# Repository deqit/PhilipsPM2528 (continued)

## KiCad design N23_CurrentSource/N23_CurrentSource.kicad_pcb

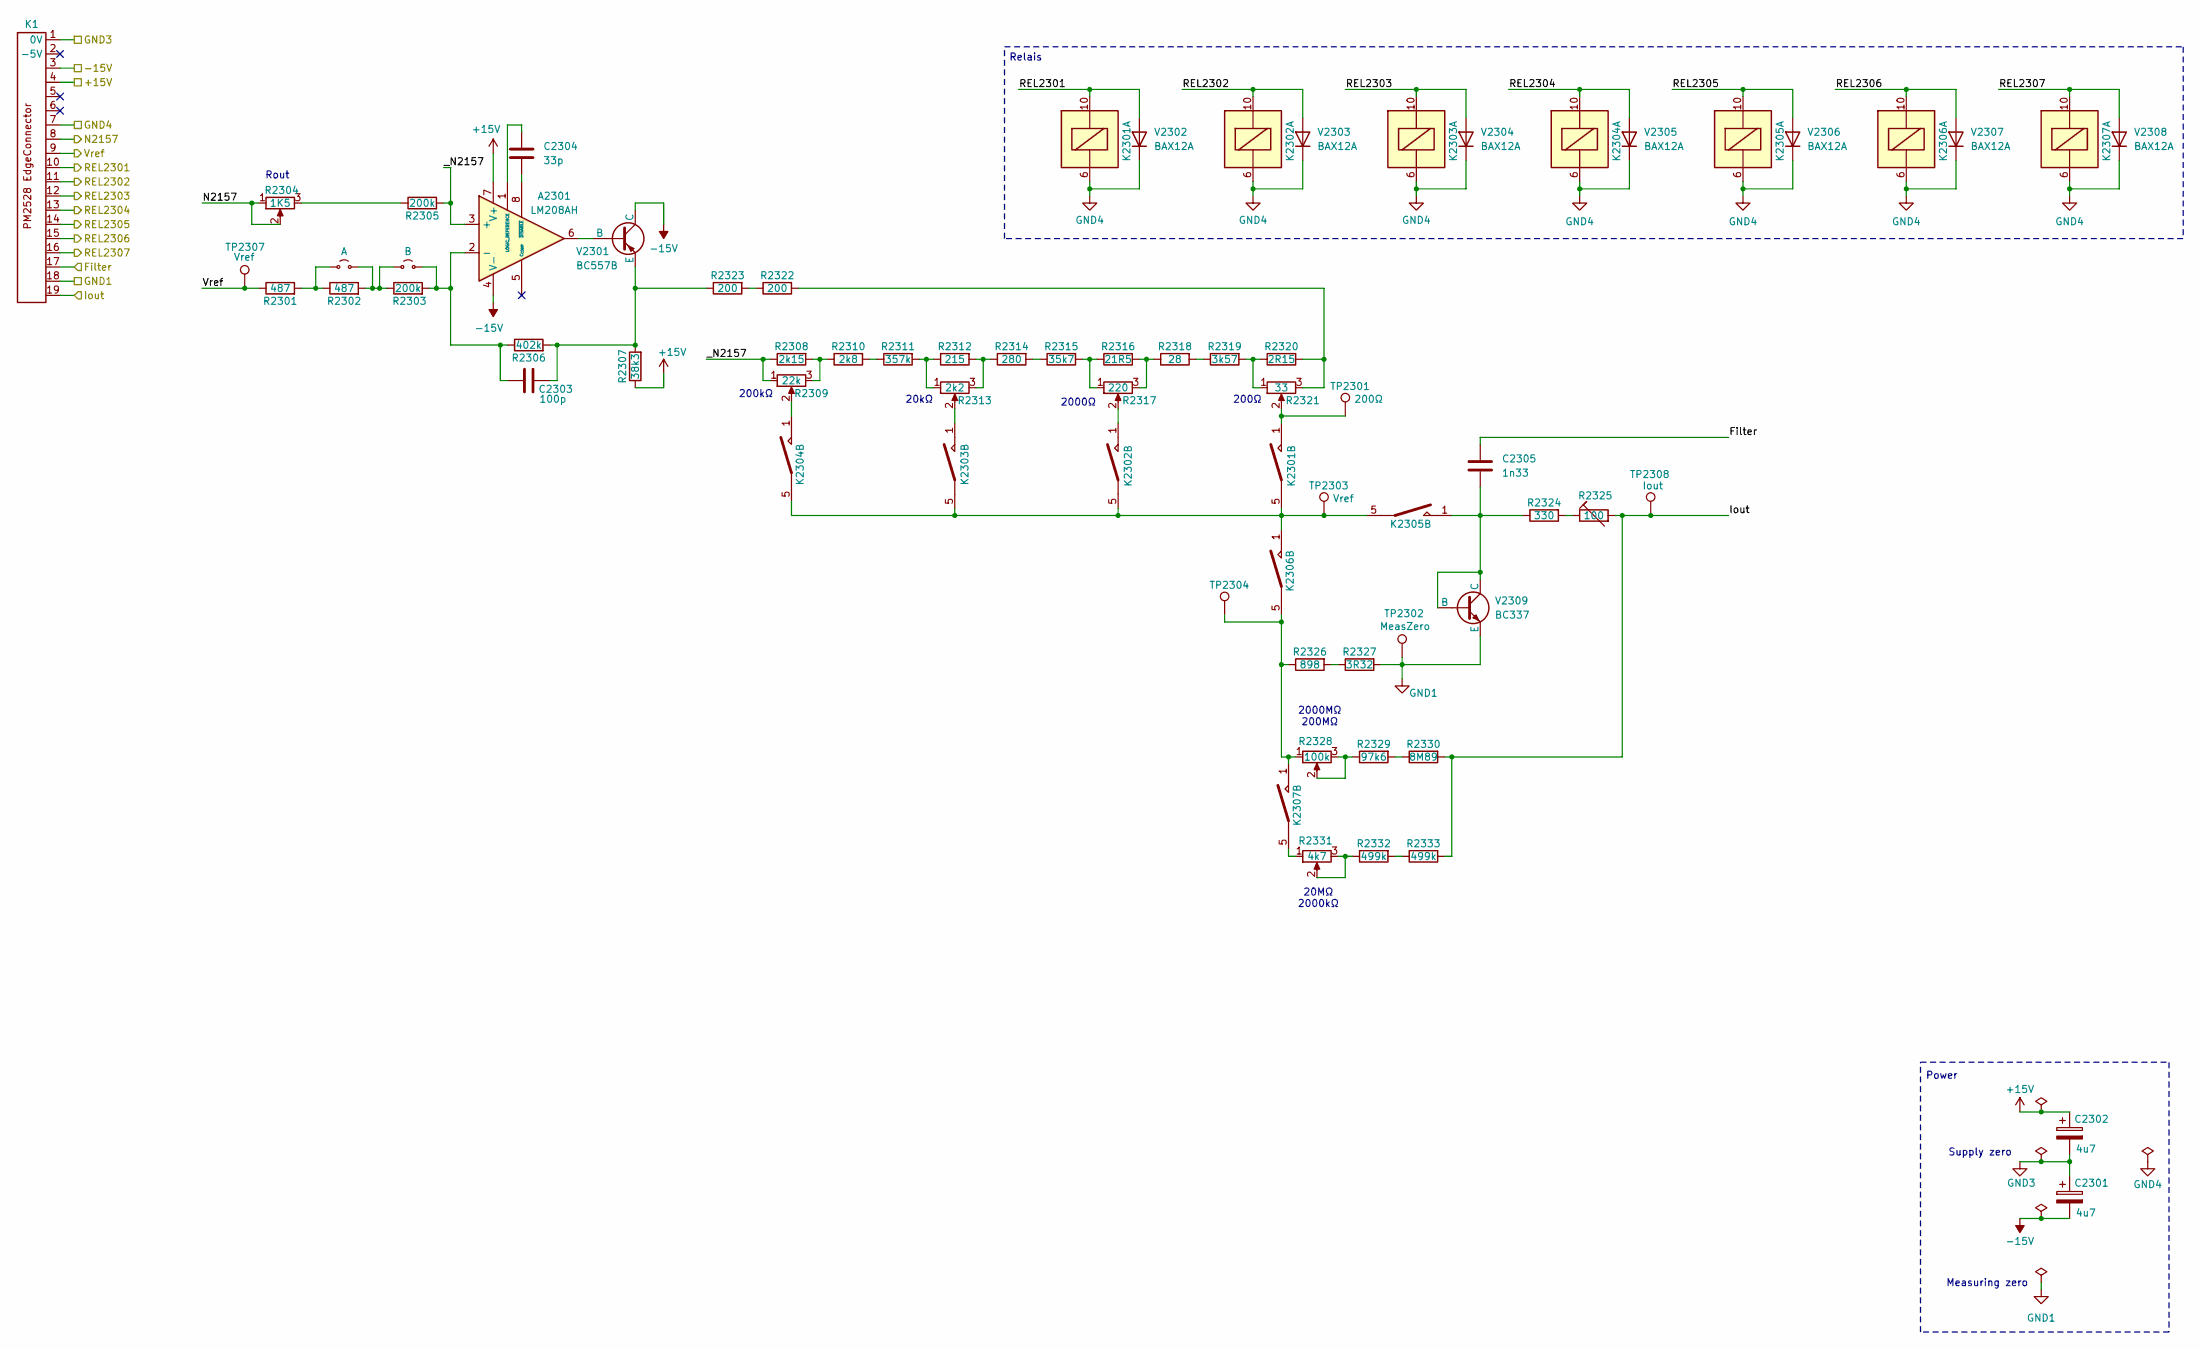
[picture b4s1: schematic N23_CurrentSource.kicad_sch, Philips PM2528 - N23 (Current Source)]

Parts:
A2301: LM208AH; TO-99-8
C2301, C2302: 4u7; C_Rect_L26.5mm_W8.5mm_P22.50mm_MKS4
C2303: 100p; C_Rect_L26.5mm_W8.5mm_P22.50mm_MKS4
C2304: 33p; C_Rect_L26.5mm_W8.5mm_P22.50mm_MKS4
C2305: 1n33; C_Rect_L26.5mm_W8.5mm_P22.50mm_MKS4
JP1: A; TestPoint_Bridge_Pitch5.08mm_Drill0.7mm
JP2: B; TestPoint_Bridge_Pitch5.08mm_Drill0.7mm
K1: PM2528_RiserCardConnector
K2301, K2302, K2303, K2304, K2305, K2306, K2307: Reed relay assy
R2301, R2302: 487; R_Axial_DIN0207_L6.3mm_D2.5mm_P10.16mm_Horizontal
R2303, R2305: 200k; R_Axial_DIN0207_L6.3mm_D2.5mm_P10.16mm_Horizontal
R2304: 1K5; Potentiometer horizontal ceramic
R2306: 402k; R_Axial_DIN0207_L6.3mm_D2.5mm_P10.16mm_Horizontal
R2307: 38k3; R_Axial_DIN0207_L6.3mm_D2.5mm_P10.16mm_Horizontal
R2308: 2k15; R_Axial_DIN0207_L6.3mm_D2.5mm_P10.16mm_Horizontal
R2309: 22k; Potentiometer horizontal ceramic
R2310: 2k8; R_Axial_DIN0207_L6.3mm_D2.5mm_P10.16mm_Horizontal
R2311: 357k; R_Axial_DIN0207_L6.3mm_D2.5mm_P10.16mm_Horizontal
R2312: 215; R_Axial_DIN0207_L6.3mm_D2.5mm_P10.16mm_Horizontal
R2313: 2k2; Potentiometer horizontal ceramic
R2314: 280; R_Axial_DIN0207_L6.3mm_D2.5mm_P10.16mm_Horizontal
R2315: 35k7; R_Axial_DIN0207_L6.3mm_D2.5mm_P10.16mm_Horizontal
R2316: 21R5; R_Axial_DIN0207_L6.3mm_D2.5mm_P10.16mm_Horizontal
R2317: 220; Potentiometer horizontal ceramic
R2318: 28; R_Axial_DIN0207_L6.3mm_D2.5mm_P10.16mm_Horizontal
R2319: 3k57; R_Axial_DIN0207_L6.3mm_D2.5mm_P10.16mm_Horizontal
R2320: 2R15; R_Axial_DIN0207_L6.3mm_D2.5mm_P10.16mm_Horizontal
R2321: 33; Potentiometer horizontal ceramic
R2322, R2323: 200; R_Axial_DIN0207_L6.3mm_D2.5mm_P10.16mm_Horizontal
R2324: 330; R_Axial_DIN0207_L6.3mm_D2.5mm_P10.16mm_Horizontal
R2325: 100; R_Axial_DIN0207_L6.3mm_D2.5mm_P10.16mm_Horizontal
R2326: 898; R_Axial_DIN0207_L6.3mm_D2.5mm_P10.16mm_Horizontal
R2327: 3R32; R_Axial_DIN0207_L6.3mm_D2.5mm_P10.16mm_Horizontal
R2328: 100k; Potentiometer horizontal ceramic
R2329: 97k6; R_Axial_DIN0207_L6.3mm_D2.5mm_P10.16mm_Horizontal
R2330: 8M89; R_Axial_DIN0207_L6.3mm_D2.5mm_P10.16mm_Horizontal
R2331: 4k7; Potentiometer horizontal ceramic
R2332, R2333: 499k; R_Axial_DIN0207_L6.3mm_D2.5mm_P10.16mm_Horizontal
TP2301: 200Ω; PinHeader_1x01_P1.00mm_Vertical
TP2302: MeasZero; PinHeader_1x01_P1.00mm_Vertical
TP2303, TP2307: Vref; PinHeader_1x01_P1.00mm_Vertical
TP2304: PinHeader_1x01_P1.00mm_Vertical
TP2308: Iout; PinHeader_1x01_P1.00mm_Vertical
V2301: BC557B; TO-92
V2302, V2303, V2304, V2305, V2306, V2307, V2308: BAX12A; D_DO-41_SOD81_P10.16mm_Horizontal
V2309: BC337; TO-92

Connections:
+15V: A2301.7 (V+), C2302.1, K1.4, R2307.1
-15V: A2301.4 (V-), C2301.2, K1.3, V2301.1 (C)
/Filter: C2305.2, K1.17
/Iout: K1.19, R2325.2, R2330.2, R2333.2, TP2308.1
/N2157: K1.8, R2304.1, R2304.2
/REL2301: K1.10, K2301.10, V2302.2 (A)
/REL2302: K1.11, K2302.10, V2303.2 (A)
/REL2303: K1.12, K2303.10, V2304.2 (A)
/REL2304: K1.13, K2304.10, V2305.2 (A)
/REL2305: K1.14, K2305.10, V2306.2 (A)
/REL2306: K1.15, K2306.10, V2307.2 (A)
/REL2307: K1.16, K2307.10, V2308.2 (A)
/Vref: K1.9, R2301.1, TP2307.1
/_N2157: A2301.3 (+), R2305.2, R2308.1, R2309.1
GND1: K1.18, R2327.2, TP2302.1, V2309.3 (E)
GND3: C2301.1, C2302.2, K1.1 (0V)
GND4: K1.7, K2301.6, K2302.6, K2303.6, K2304.6, K2305.6, K2306.6, K2307.6, V2302.1 (K), V2303.1 (K), V2304.1 (K), V2305.1 (K), V2306.1 (K), V2307.1 (K), V2308.1 (K)
unnamed: A2301.2 (-), C2303.2, JP2.2 (B), R2303.2, R2306.1
unnamed: A2301.1 (LOGIC_REFERENCE), C2304.1
unnamed: A2301.8 (~DISABLE), C2304.2
unnamed: JP1.1 (A), R2301.2, R2302.1
unnamed: JP1.2 (B), JP2.1 (A), R2302.2, R2303.1
unnamed: K2301.1, R2321.2, TP2301.1
unnamed: K2301.5, K2302.5, K2303.5, K2304.5, K2305.5, K2306.1, TP2303.1
unnamed: K2302.1, R2317.2
unnamed: K2303.1, R2313.2
unnamed: K2304.1, R2309.2
unnamed: K2306.5, K2307.1, R2326.1, R2328.1, TP2304.1
unnamed: K2307.5, R2331.1
unnamed: R2304.3, R2305.1
unnamed: R2308.2, R2309.3, R2310.1
unnamed: R2310.2, R2311.1
unnamed: R2311.2, R2312.1, R2313.1
unnamed: R2312.2, R2313.3, R2314.1
unnamed: R2314.2, R2315.1
unnamed: R2315.2, R2316.1, R2317.1
unnamed: R2316.2, R2317.3, R2318.1
unnamed: R2318.2, R2319.1
unnamed: R2319.2, R2320.1, R2321.1
unnamed: R2320.2, R2321.3, R2322.2
unnamed: R2322.1, R2323.2
unnamed: R2324.2, R2325.1
unnamed: R2326.2, R2327.1
unnamed: R2328.2, R2328.3, R2329.1
unnamed: R2329.2, R2330.1
unnamed: R2331.2, R2331.3, R2332.1
unnamed: R2332.2, R2333.1
unnamed: A2301.6, V2301.2 (B)
unnamed: C2303.1, R2306.2, R2307.2, R2323.1, V2301.3 (E)
unnamed: C2305.1, K2305.1, R2324.1, V2309.1 (C), V2309.2 (B)

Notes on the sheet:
200Ω
Power
Measuring zero
20kΩ
2000MΩ 200MΩ
200kΩ
20MΩ 2000kΩ
Relais
2000Ω
Rout
Supply zero

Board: 2 copper layers, 64 parts (0 on the bottom side), 50 nets, no tracks yet.

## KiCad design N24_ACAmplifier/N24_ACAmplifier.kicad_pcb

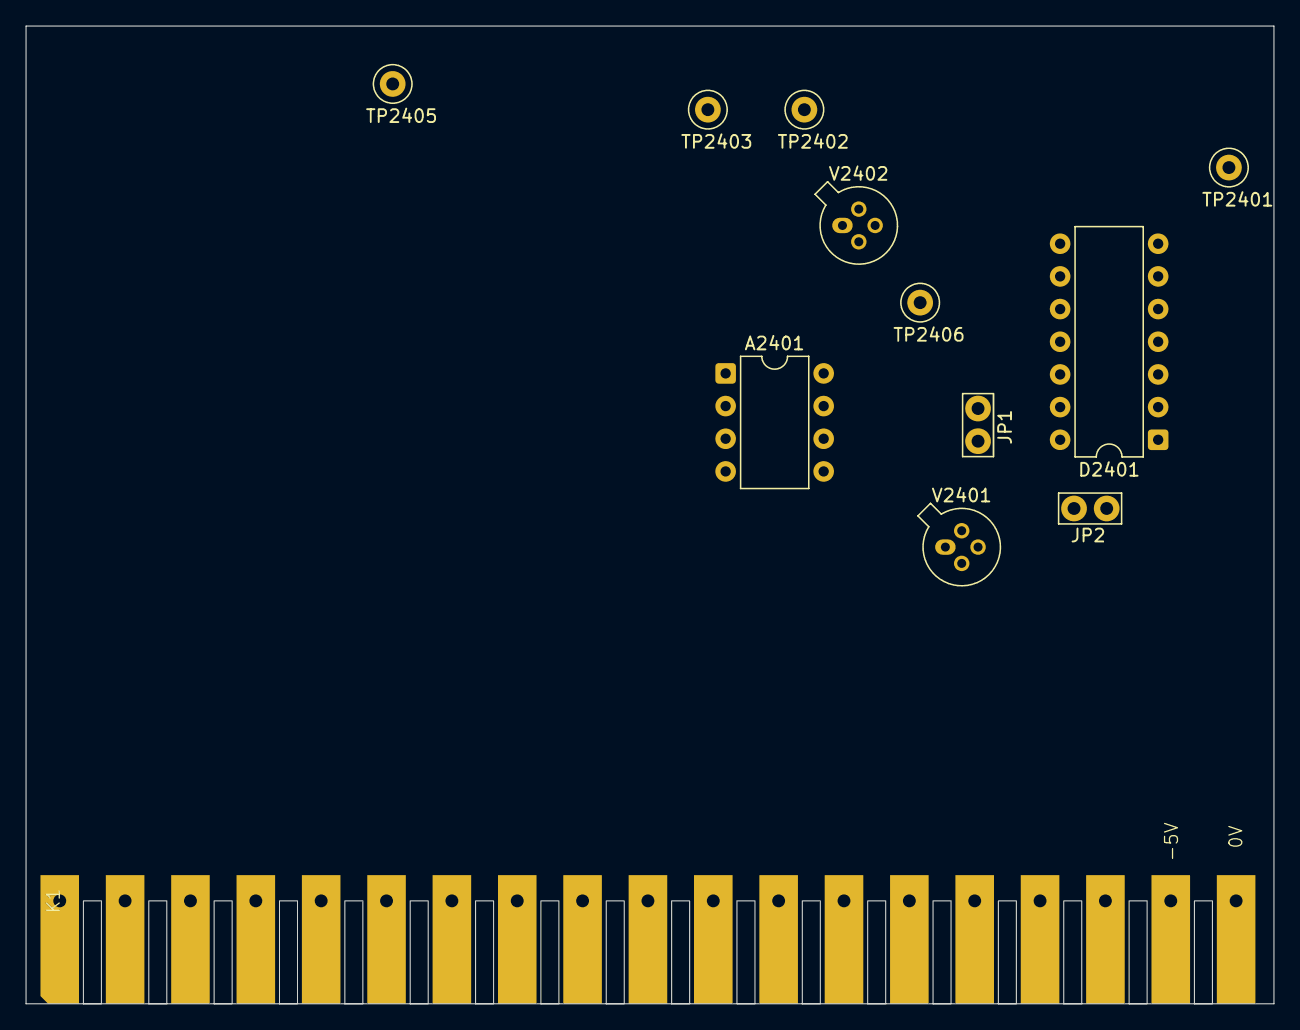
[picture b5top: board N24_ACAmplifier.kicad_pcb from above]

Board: 2 copper layers, 97.0 x 76.0 mm, 12 parts (0 on the bottom side), 11 nets, no tracks yet.

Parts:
A2401: LM308AH; DIP-8_W7.62mm
D2401: HEF4047; DIP-14_W7.62mm
JP1: A; TestPoint_Bridge_Pitch2.54mm_Drill1.0mm
JP2: B; TestPoint_Bridge_Pitch2.54mm_Drill1.0mm
K1: PM2528_RiserCardConnector
TP2401: V.Chopper; TestPoint_Loop_D2.50mm_Drill1.0mm
TP2402, TP2403: TestPoint_Loop_D2.50mm_Drill1.0mm
TP2405: 0V; TestPoint_Loop_D2.50mm_Drill1.0mm
TP2406: AC_RMS?; TestPoint_Loop_D2.50mm_Drill1.0mm
V2401: BSV81; TO-72-4
V2402: BFW13; TO-72-4

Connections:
+15V: A2401.7 (V+), K1.4
-5V: D2401.7 (VSS), D2401.8 (+TRIGGER), D2401.9 (EXT_RESET), D2401.12 (RETRIGGER), K1.2 (-5V)
-15V: A2401.4 (V-), K1.3
GND2: D2401.4 (~ASTABLE), D2401.5 (ASTABLE), D2401.6 (-TRIGGER), D2401.14 (VDD), K1.1 (0V)
GND4: K1.9, K1.11, V2402.3 (D)
GND5: K1.13, TP2405.1
unnamed: A2401.6, TP2406.1
unnamed: D2401.10 (Q), TP2401.1, V2402.1 (G)
unnamed: D2401.11 (~Q), V2401.2 (G)
unnamed: V2401.3 (S), V2401.4 (Bulk)
unnamed: TP2402.1, V2402.2 (S)

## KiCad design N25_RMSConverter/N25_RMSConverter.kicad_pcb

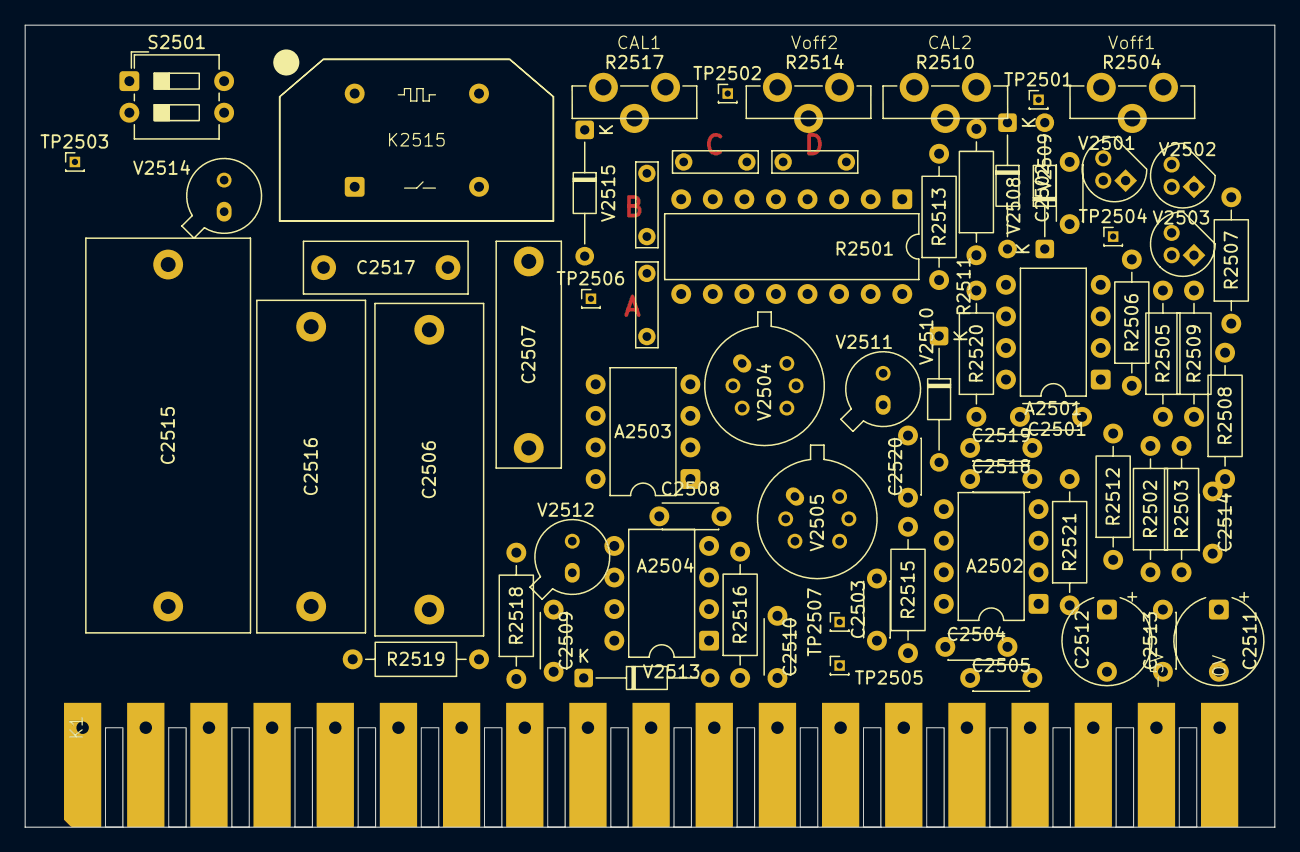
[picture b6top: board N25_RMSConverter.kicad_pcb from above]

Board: 2 copper layers, 100.5 x 64.5 mm, 72 parts (0 on the bottom side), 51 nets, no tracks yet.

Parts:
A2501, A2503, A2504: LM308AN; DIP-8_W7.62mm
A2502: LF356BN; DIP-8_W7.62mm
C2501: 22p; C_Disc_D4.3mm_W1.9mm_P5.00mm
C2502, C2510: 470p; C_Disc_D4.3mm_W1.9mm_P5.00mm
C2503, C2509: 100p; C_Disc_D4.3mm_W1.9mm_P5.00mm
C2504, C2505, C2518: 10n; C_Disc_D4.3mm_W1.9mm_P5.00mm
C2506: 3u3; C_Rect_L26.5mm_W8.5mm_P22.50mm_MKS4
C2507: 330n; C_Rect_L18.0mm_W5.0mm_P15.00mm_FKS3_FKP3
C2508: 10p; C_Disc_D4.3mm_W1.9mm_P5.00mm
C2511, C2512: 6u8; CP_Radial_Tantal_D7.0mm_P5.00mm
C2513, C2514: 22n; C_Disc_D4.3mm_W1.9mm_P5.00mm
C2515: 6u8; C_Rect_L31.5mm_W13.0mm_P27.50mm_MKS4
C2516: 2u2; C_Rect_L26.5mm_W8.5mm_P22.50mm_MKS4
C2517: 100n; C_Rect_L13.0mm_W4.0mm_P10.00mm_FKS3_FKP3_MKS4
C2519: 2n2; C_Disc_D4.3mm_W1.9mm_P5.00mm
C2520: 18p; C_Disc_D4.3mm_W1.9mm_P5.00mm
JP1: D; TestPoint_Bridge_Pitch5.08mm_Drill0.7mm
JP2: C; TestPoint_Bridge_Pitch5.08mm_Drill0.7mm
JP3: B; TestPoint_Bridge_Pitch5.08mm_Drill0.7mm
JP4: A; TestPoint_Bridge_Pitch5.08mm_Drill0.7mm
K1: PM2528_RiserCardConnector
K2515: Reed relay assy
R2501: OM529; DIP-16_W7.62mm
R2502: 19R6; R_Axial_DIN0207_L6.3mm_D2.5mm_P10.16mm_Horizontal
R2503, R2513: 301k; R_Axial_DIN0207_L6.3mm_D2.5mm_P10.16mm_Horizontal
R2504, R2514: 47k; Potentiometer horizontal ceramic
R2505: 750; R_Axial_DIN0207_L6.3mm_D2.5mm_P10.16mm_Horizontal
R2506: 590; R_Axial_DIN0207_L6.3mm_D2.5mm_P10.16mm_Horizontal
R2507: 301; R_Axial_DIN0207_L6.3mm_D2.5mm_P10.16mm_Horizontal
R2508: 7k87; R_Axial_DIN0207_L6.3mm_D2.5mm_P10.16mm_Horizontal
R2509: 1k96; R_Axial_DIN0207_L6.3mm_D2.5mm_P10.16mm_Horizontal
R2510: 1K; Potentiometer horizontal ceramic
R2511: 8R25; R_Axial_DIN0207_L6.3mm_D2.5mm_P10.16mm_Horizontal
R2512: 115; R_Axial_DIN0207_L6.3mm_D2.5mm_P10.16mm_Horizontal
R2515, R2518: 2k05; R_Axial_DIN0207_L6.3mm_D2.5mm_P10.16mm_Horizontal
R2516: 4k02; R_Axial_DIN0207_L6.3mm_D2.5mm_P10.16mm_Horizontal
R2517: 330; Potentiometer horizontal ceramic
R2519: 3k01; R_Axial_DIN0207_L6.3mm_D2.5mm_P10.16mm_Horizontal
R2520: 5M6; R_Axial_DIN0207_L6.3mm_D2.5mm_P10.16mm_Horizontal
R2521: 33M; R_Axial_DIN0207_L6.3mm_D2.5mm_P10.16mm_Horizontal
S2501: SW_DPST_x2; SW_DIP_SPSTx02_Slide_6.7x6.64mm_W7.62mm_P2.54mm_LowProfile
TP2501, TP2502, TP2504, TP2507: PinHeader_1x01_P1.00mm_Vertical
TP2503: OUT; PinHeader_1x01_P1.00mm_Vertical
TP2505: IN; PinHeader_1x01_P1.00mm_Vertical
TP2506: 0V; PinHeader_1x01_P1.00mm_Vertical
V2501, V2502: BC547B; TO-92
V2503: BC559B; TO-92
V2504, V2505: MAT01GH; TO-78-6
V2508, V2509, V2513: BAW62; D_DO-34_SOD68_P10.16mm_Horizontal
V2510: BZX79-B4V7; D_DO-34_SOD68_P10.16mm_Horizontal
V2511, V2512, V2514: BAV45; TO-18-2
V2515: BAX12A; D_DO-34_SOD68_P10.16mm_Horizontal

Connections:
+5V: K1.5, R2518.2
+15V: A2501.7 (V+), A2502.7 (V+), A2503.7 (V+), A2504.7 (V+), C2504.1, C2511.1, C2513.1, K1.4, R2504.1, R2505.2, R2506.2, R2514.1
-15V: A2501.4 (V-), A2502.4 (V-), A2503.4 (V-), A2504.4 (V-), C2505.2, C2512.2, C2514.2, K1.3, R2504.3, R2507.1, R2509.1, R2514.3, V2510.2 (A)
/D1703.22: K1.15, K2515.10, V2515.2 (A)
/IN: C2518.2, K1.7, R2501.16, R2521.1, TP2505.1
/OUT: C2516.2, C2517.2, K1.13, R2501.10, TP2503.1, V2514.2 (A)
GND3: C2504.2, C2505.1, C2511.2, C2512.1, C2513.2, C2514.1, K1.1 (0V), R2508.1, R2519.1, TP2506.1
GND4: A2503.3 (+), A2504.3 (+), K1.8, K1.12, R2502.1, R2512.1, V2504.2 (B), V2504.5 (B)
GND5: C2509.2, C2517.1, K1.11, K2515.5, S2501.3 (A)
GND6: K1.14, K2515.6, V2515.1 (K)
unnamed: A2501.3 (+), R2502.2, R2503.2
unnamed: A2501.2 (-), C2502.2, R2510.2, TP2501.1
unnamed: A2501.1 (CompenA), C2501.2
unnamed: A2501.8 (CompenB), C2501.1
unnamed: A2502.3 (+), R2512.2, R2513.2
unnamed: A2502.2 (-), C2519.2, C2520.1, R2501.15, V2504.1 (C), V2511.1 (K)
unnamed: A2503.2 (-), C2506.1, C2507.1, R2501.13, V2505.6 (C)
unnamed: A2503.1 (CompenA), C2508.2
unnamed: A2503.8 (CompenB), C2508.1
unnamed: A2504.2 (-), C2510.2, R2517.1, R2517.2, V2504.6 (C), V2512.1 (K)
unnamed: A2504.8 (CompenB), C2509.1
unnamed: C2515.2, R2501.11
unnamed: C2518.1, R2520.2
unnamed: C2519.1, R2521.2
unnamed: JP1.1 (A), R2501.5
unnamed: JP2.1 (A), R2501.6
unnamed: JP3.1 (A), R2501.7
unnamed: JP4.1 (A), R2501.8, R2517.3
unnamed: K2515.1, R2501.9
unnamed: R2501.1, R2510.3, R2511.1, R2520.1
unnamed: R2501.3, R2510.1, R2511.2
unnamed: R2503.1, R2504.2
unnamed: R2513.1, R2514.2
unnamed: C2506.2, S2501.1 (A)
unnamed: A2503.6, C2507.2, R2501.12, S2501.2 (B), TP2502.1
unnamed: C2515.1, C2516.1, S2501.4 (B)
unnamed: A2501.6, V2501.2 (B), V2510.1 (K)
unnamed: R2505.1, V2501.1 (C), V2503.2 (B)
unnamed: R2507.2, V2501.3 (E), V2502.3 (E)
unnamed: C2502.1, R2508.2, R2509.2, V2502.2 (B)
unnamed: V2502.1 (C), V2503.1 (C), V2508.2 (A), V2509.1 (K)
unnamed: R2506.1, V2503.3 (E)
unnamed: V2504.3 (E), V2505.1 (C), V2505.2 (B)
unnamed: V2504.4 (E), V2505.5 (B), V2513.2 (A)
unnamed: C2503.2, R2515.2, TP2507.1, V2505.3 (E), V2505.4 (E)
unnamed: R2501.14, TP2504.1, V2508.1 (K)
unnamed: R2501.2, V2509.2 (A)
unnamed: A2502.6, C2503.1, C2520.2, R2515.1, V2511.2 (A)
unnamed: A2504.6, C2510.1, R2516.2, V2512.2 (A)
unnamed: R2516.1, V2513.1 (K)
unnamed: R2518.1, R2519.2, V2514.1 (K)

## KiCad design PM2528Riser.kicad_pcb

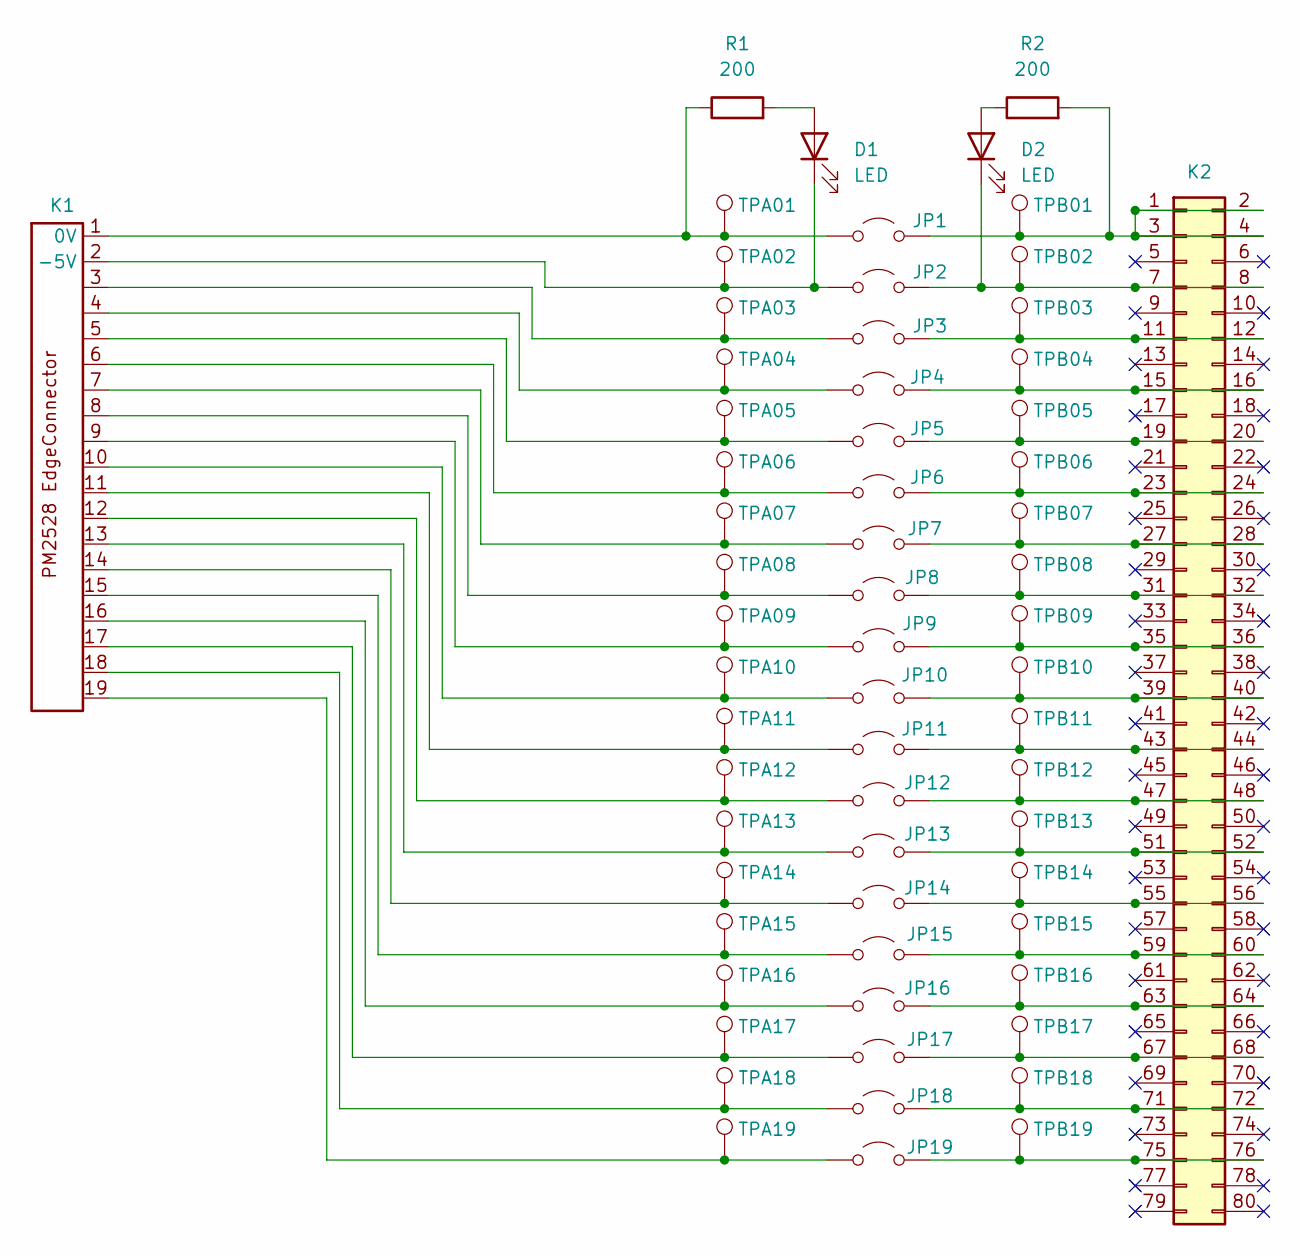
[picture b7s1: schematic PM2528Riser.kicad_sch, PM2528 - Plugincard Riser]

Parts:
D1, D2: LED; LED_0805_2012Metric
JP1, JP2, JP3, JP4, JP5, JP6, JP7, JP8, JP9, JP10, JP11, JP12, JP13, JP14, JP15, JP16, JP17, JP18, JP19: Jumper_2_Open; PinHeader_1x02_P2.54mm_Vertical
K1: PM2528_RiserCardConnector
K2: Conn_02x40_Odd_Even; PinHeader_2x40_P2.54mm_Vertical
R1, R2: 200; R_0805_2012Metric_Pad1.20x1.40mm_HandSolder
TPA01, TPA02, TPA03, TPA04, TPA05, TPA06, TPA07, TPA08, TPA09, TPA10, TPA11, TPA12, TPA13, TPA14, TPA15, TPA16, TPA17, TPA18, TPA19: TestPoint; TestPoint_THTPad_2.0x2.0mm_Drill1.0mm
TPB01, TPB02, TPB03, TPB04, TPB05, TPB06, TPB07, TPB08, TPB09, TPB10, TPB11, TPB12, TPB13, TPB14, TPB15, TPB16, TPB17, TPB18, TPB19: TestPoint; TestPoint_THTPad_2.0x2.0mm_Drill1.0mm

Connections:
unnamed: D1.2 (A), R1.2
unnamed: D1.1 (K), JP2.1 (A), K1.2 (-5V), TPA02.1
unnamed: D2.2 (A), R2.1
unnamed: D2.1 (K), JP2.2 (B), K2.7, K2.8, TPB02.1
unnamed: JP1.1 (A), K1.1 (0V), R1.1, TPA01.1
unnamed: JP1.2 (B), K2.1, K2.2, K2.3, K2.4, R2.2, TPB01.1
unnamed: JP3.1 (A), K1.3, TPA03.1
unnamed: JP3.2 (B), K2.11, K2.12, TPB03.1
unnamed: JP4.1 (A), K1.4, TPA04.1
unnamed: JP4.2 (B), K2.15, K2.16, TPB04.1
unnamed: JP5.1 (A), K1.5, TPA05.1
unnamed: JP5.2 (B), K2.19, K2.20, TPB05.1
unnamed: JP6.1 (A), K1.6, TPA06.1
unnamed: JP6.2 (B), K2.23, K2.24, TPB06.1
unnamed: JP7.1 (A), K1.7, TPA07.1
unnamed: JP7.2 (B), K2.27, K2.28, TPB07.1
unnamed: JP8.1 (A), K1.8, TPA08.1
unnamed: JP8.2 (B), K2.31, K2.32, TPB08.1
unnamed: JP9.1 (A), K1.9, TPA09.1
unnamed: JP9.2 (B), K2.35, K2.36, TPB09.1
unnamed: JP10.1 (A), K1.10, TPA10.1
unnamed: JP10.2 (B), K2.39, K2.40, TPB10.1
unnamed: JP11.1 (A), K1.11, TPA11.1
unnamed: JP11.2 (B), K2.43, K2.44, TPB11.1
unnamed: JP12.1 (A), K1.12, TPA12.1
unnamed: JP12.2 (B), K2.47, K2.48, TPB12.1
unnamed: JP13.1 (A), K1.13, TPA13.1
unnamed: JP13.2 (B), K2.51, K2.52, TPB13.1
unnamed: JP14.1 (A), K1.14, TPA14.1
unnamed: JP14.2 (B), K2.55, K2.56, TPB14.1
unnamed: JP15.1 (A), K1.15, TPA15.1
unnamed: JP15.2 (B), K2.59, K2.60, TPB15.1
unnamed: JP16.1 (A), K1.16, TPA16.1
unnamed: JP16.2 (B), K2.63, K2.64, TPB16.1
unnamed: JP17.1 (A), K1.17, TPA17.1
unnamed: JP17.2 (B), K2.67, K2.68, TPB17.1
unnamed: JP18.1 (A), K1.18, TPA18.1
unnamed: JP18.2 (B), K2.71, K2.72, TPB18.1
unnamed: JP19.1 (A), K1.19, TPA19.1
unnamed: JP19.2 (B), K2.75, K2.76, TPB19.1

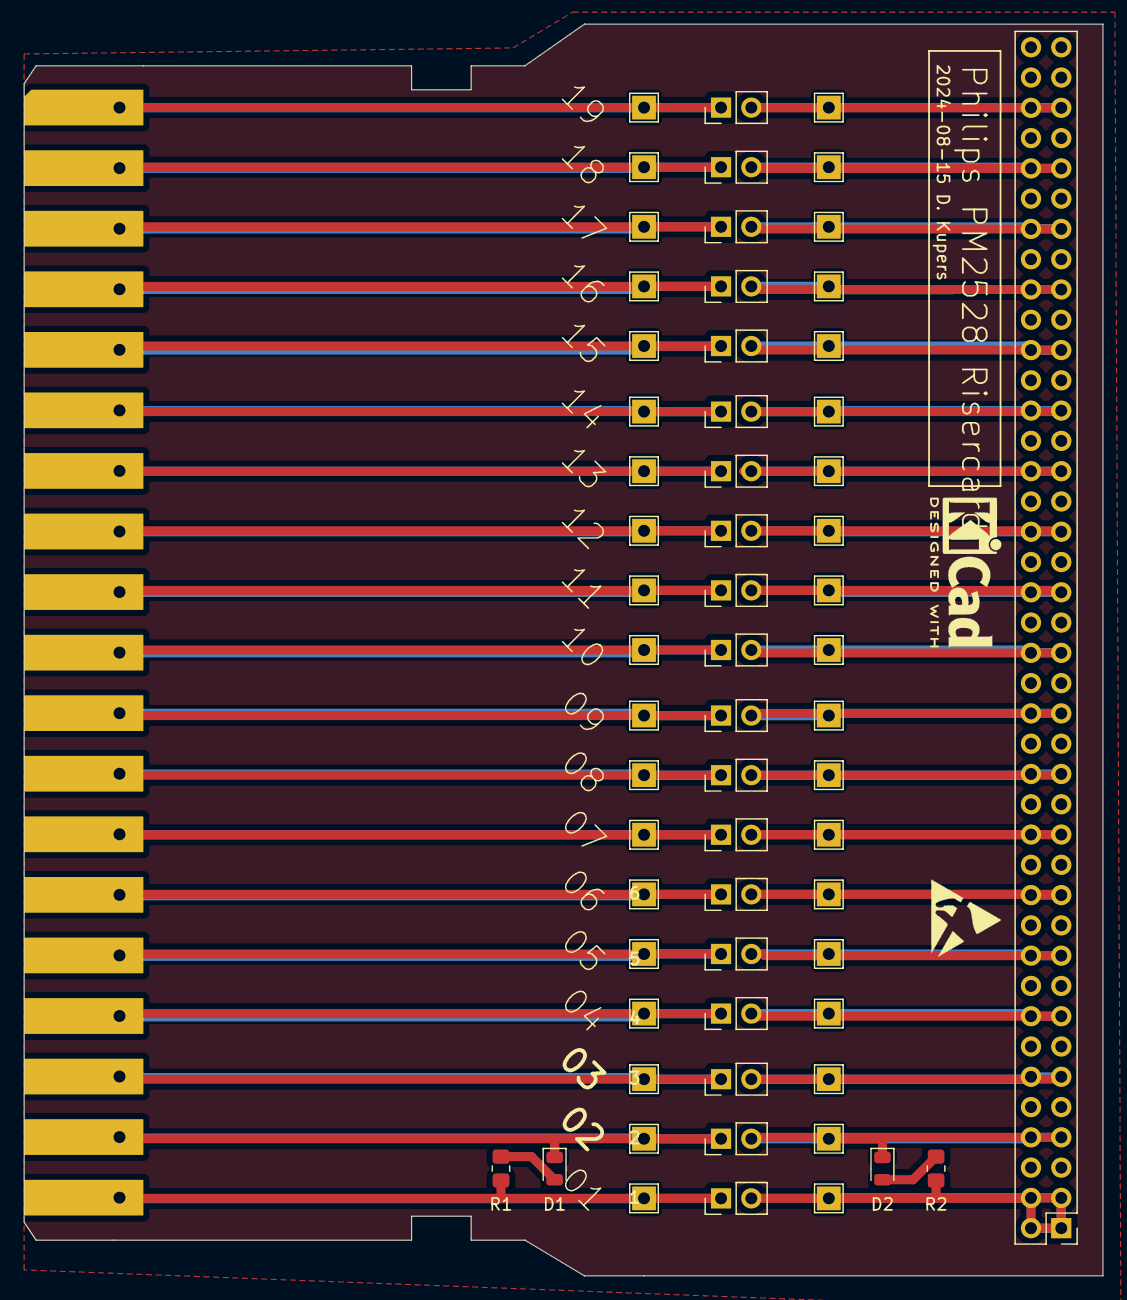
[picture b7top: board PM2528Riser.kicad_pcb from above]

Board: 2 copper layers, 90.5 x 105.0 mm, 63 parts (0 on the bottom side), 40 nets.
